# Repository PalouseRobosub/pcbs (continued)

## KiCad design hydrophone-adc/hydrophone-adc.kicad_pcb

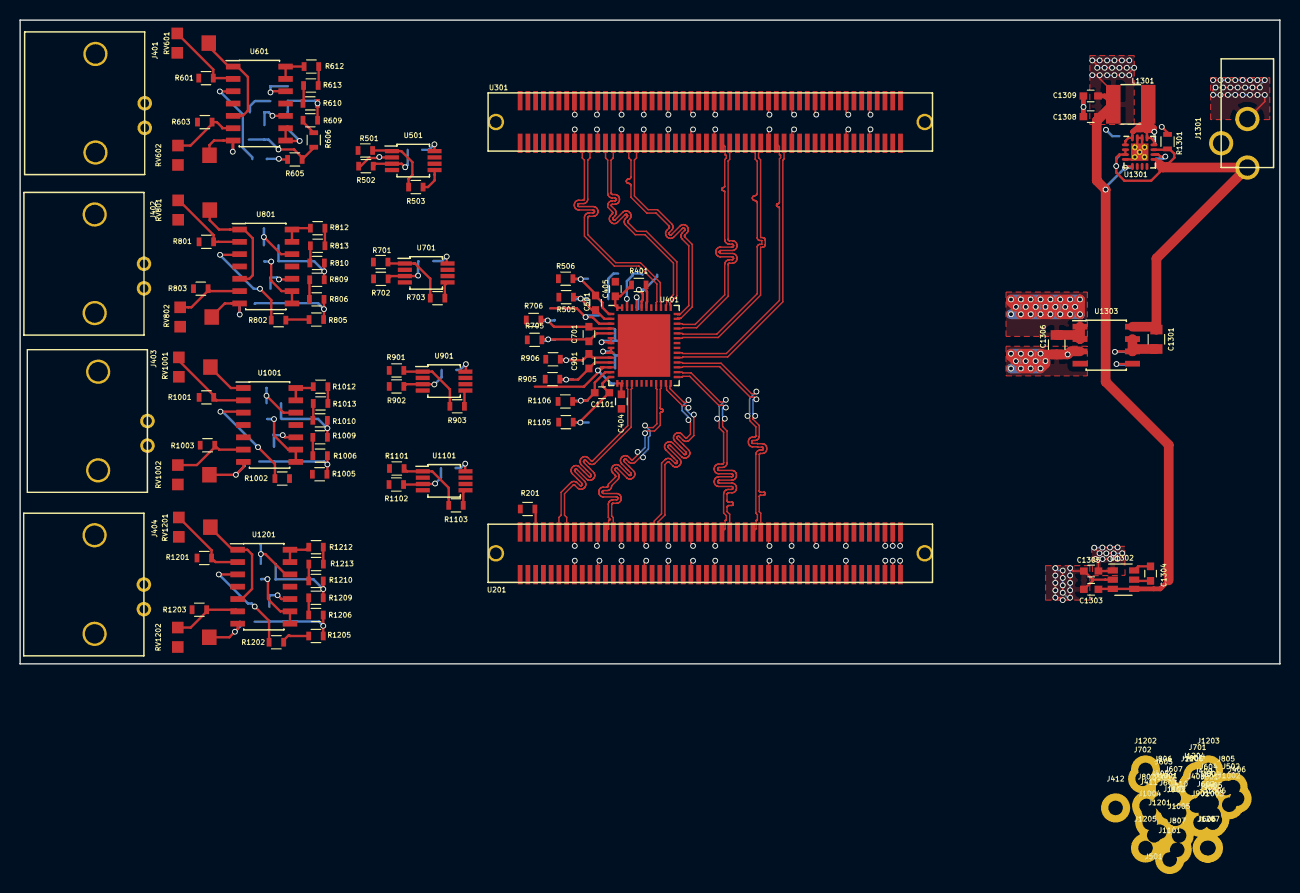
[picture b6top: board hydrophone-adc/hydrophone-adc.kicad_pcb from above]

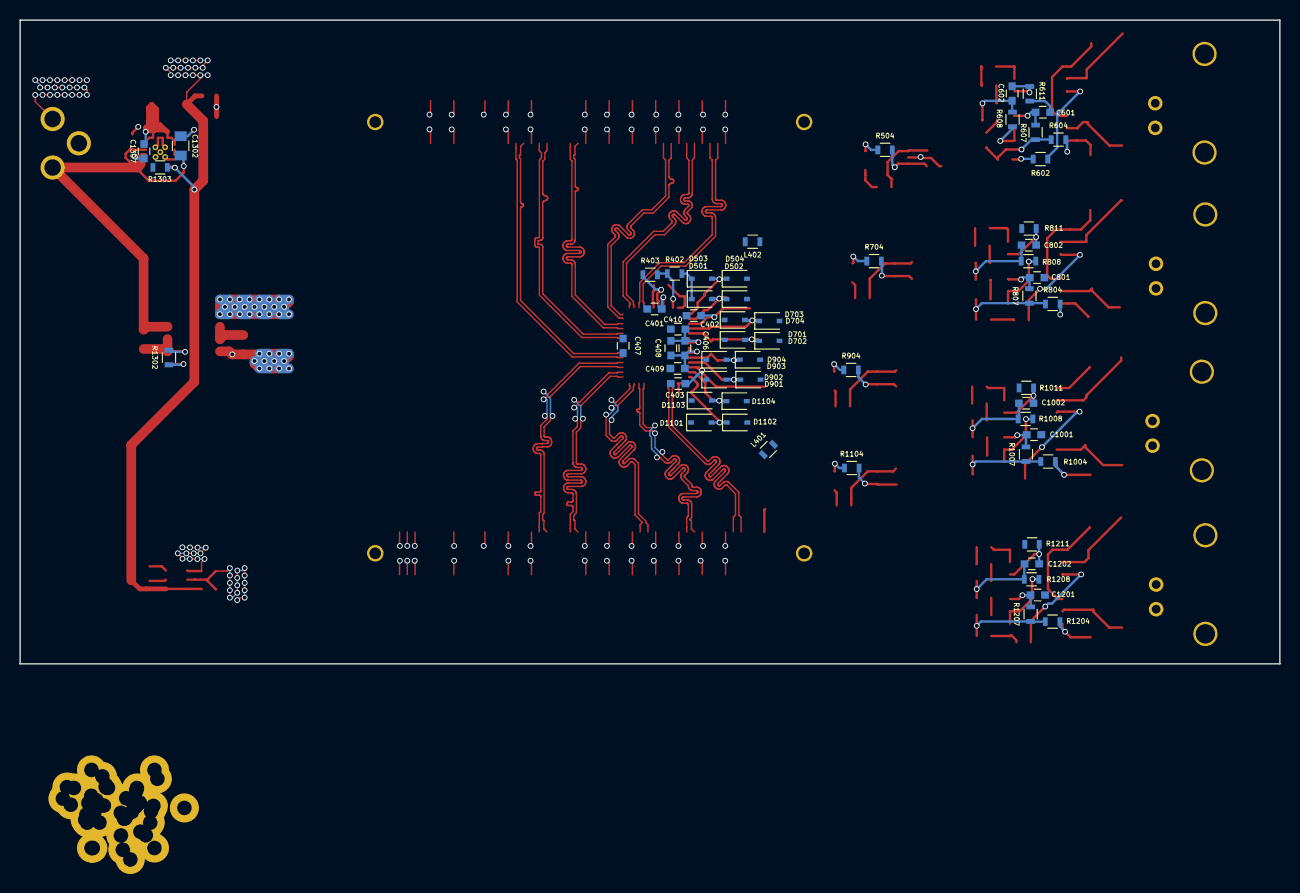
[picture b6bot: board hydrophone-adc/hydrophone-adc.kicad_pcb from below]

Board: 4 copper layers, 129.8 x 66.3 mm, 204 parts (61 on the bottom side), 126 nets.

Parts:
C401, C1304: 1u; C_0603
C402, C403, C404, C405, C406, C407, C409, C410: 100n; C_0603
C408, C1303, C1305: 2.2u; C_0603
C501, C701, C901, C1101: 10n; C_0603
C601, C602, C801, C802, C1001, C1002, C1201, C1202: 1n; C_0603
C1301, C1302, C1306: 10u; C_0805
C1307: 22n; C_0603
C1308, C1309: 22u; C_0603
D501, D502, D503, D504, D701, D702, D703, D704, D901, D902, D903, D904, D1101, D1102, D1103, D1104: D_Schottky; D_SOD-323
J401, J402, J403, J404: CONN_COAXIAL; BNC-Coax-TE
J405, J406, J407, J408, J409, J410, J411, J412, J501, J502, J601, J602, J603, J604, J605, J606, J607, J701, J702, J801, J802, J803, J804, J805, J806, J807, J901, J902, J1001, J1002, J1003, J1004, J1005, J1006, J1007, J1101, J1102, J1201, J1202, J1203, J1204, J1205, J1206, J1207: TEST_1P; Measurement_Point_Round-TH_Big
J1301: BARREL_JACK; BarrelJack-CUI
L401, L402: Ferrite_Bead; R_0603
L1301: 4.7u; Inductor-3.6mm-Pitch-4.0mm-Length-1.5mm-Width
R201, R601, R603, R607, R801, R803, R807, R1001, R1003, R1007, R1201, R1203, R1207, R1301, R1303: 10k; R_0603
R401: 2k; R_0603
R402, R403, R602, R604, R605, R606, R608, R609, R610, R612, R613, R802, R804, R805, R806, R808, R809, R810, R812, R813, R1002, R1004, R1005, R1006, R1008, R1009, R1010, R1012, R1013, R1202, R1204, R1205, R1206, R1208, R1209, R1210, R1212, R1213: 0; R_0603
R501, R502, R503, R504, R701, R702, R703, R704, R901, R902, R903, R904, R1101, R1102, R1103, R1104: 10k .1%; R_0603
R505, R506, R705, R706, R905, R906, R1105, R1106: 100; R_0603
R611, R811, R1011, R1211: 3.16k; R_0603
R1302: 100k; R_0603
RV601, RV602, RV801, RV802, RV1001, RV1002, RV1201, RV1202: POT; TC33X-2
U201: micro-zed-jx1; fci-61083-2x50
U301: micro-zed-jx2; fci-61083-2x50
U401: LTC2171-14; QFN-52-1EP_7x8mm_Pitch0.5mm
U501, U701, U901, U1101: el5170; MSOP-8_3x3mm_Pitch0.65mm
U601, U801, U1001, U1201: LM324; SOIC-14_3.9x8.7mm_Pitch1.27mm
U1301: TS30013; QFN-16-1EP_3x3mm_Pitch0.5mm_ThermalVias
U1302: LM2776; SOT-23-6
U1303: LT1963; SOIC-8_3.9x4.9mm_Pitch1.27mm

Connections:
+1V8: C404.1, C405.1, C407.1, C1306.1, D501.1, D503.1, D701.1, D703.1, D901.1, D903.1, D1101.1, D1103.1, R401.1, R402.2, U201.78, U201.79, U201.80, U301.78, U301.79, U301.80, U401.15, U401.16, U401.34, U401.51, U401.52, U1303.1, U1303.2
+5V: C1303.1, C1308.1, C1309.1, L1301.2, R201.1, R1303.1, U201.57, U201.58, U201.59, U201.60, U301.12, U301.57, U301.58, U301.59, U301.60, U501.6, U601.4, U701.6, U801.4, U901.6, U1001.4, U1101.6, U1201.4, U1301.5, U1302.3, U1302.4
-5V: C1305.1, U501.7, U601.11, U701.7, U801.11, U901.7, U1001.11, U1101.7, U1201.11, U1302.1
/ADC/Diff Conv1/Vin: R501.2, R612.1, R613.1
/ADC/Diff Conv1/Vout+: C501.2, D503.2, D504.1, J406.1, J502.1, R506.2, U401.1
/ADC/Diff Conv1/Vout-: C501.1, D501.2, D502.1, J405.1, J501.1, R505.2, U401.2
/ADC/Diff Conv2/Vin: R701.2, R812.1, R813.1
/ADC/Diff Conv2/Vout+: C701.2, D703.2, D704.1, J408.1, J702.1, R706.2, U401.4
/ADC/Diff Conv2/Vout-: C701.1, D701.2, D702.1, J407.1, J701.1, R705.2, U401.5
/ADC/Diff Conv3/Vin: R901.2, R1012.1, R1013.1
/ADC/Diff Conv3/Vout+: C901.2, D903.2, D904.1, J410.1, J902.1, R906.2, U401.10
/ADC/Diff Conv3/Vout-: C901.1, D901.2, D902.1, J409.1, J901.1, R905.2, U401.11
/ADC/Diff Conv4/Vin: R1101.2, R1212.1, R1213.1
/ADC/Diff Conv4/Vout+: C1101.2, D1103.2, D1104.1, J412.1, J1102.1, R1106.2, U401.13
/ADC/Diff Conv4/Vout-: C1101.1, D1101.2, D1102.1, J411.1, J1101.1, R1105.2, U401.14
/ADC/Filter1/Vin: J401.1, J601.1, R602.1, U601.3
/ADC/Filter2/Vin: J402.1, J801.1, R802.1, U801.3
/ADC/Filter3/Vin: J403.1, J1001.1, R1002.1, U1001.3
/ADC/Filter4/Vin: J404.1, J1201.1, R1202.1, U1201.3
/ADC/MISO: R401.2, U401.46
/ADC/Vcm12: C402.1, U401.3, U501.4, U701.4
/ADC/Vcm34: C403.1, U401.12, U901.4, U1101.4
/Power/Vin: C1301.1, C1302.1, J1301.1, R1301.1, U1301.2, U1301.3, U1301.9, U1301.11, U1303.8
/data_clk+: U301.62, U401.36
/data_clk-: U301.64, U401.35
/fr_clk+: U301.68, U401.32
/fr_clk-: U301.70, U401.31
/out1a+: U301.18, U401.44
/out1a-: U301.20, U401.43
/out1b+: U301.24, U401.42
/out1b-: U301.26, U401.41
/out2a+: U301.30, U401.40
/out2a-: U301.32, U401.39
/out2b+: U301.54, U401.38
/out2b-: U301.56, U401.37
/out3a+: U201.61, U401.30
/out3a-: U201.63, U401.29
/out3b+: U201.53, U401.28
/out3b-: U201.55, U401.27
/out4a+: U201.35, U401.26
/out4a-: U201.37, U401.25
/out4b+: U201.23, U401.24
/out4b-: U201.25, U401.23
/samp_clk+: U201.11, U401.17
/samp_clk-: U201.13, U401.18
/v_good: R1303.2, U301.11, U1301.8
/vccio_en: R1302.1, U301.10, U1303.5
GND: C407.2, C1301.2, C1302.2, C1303.2, C1305.2, C1306.2, C1308.2, C1309.2, J1301.2, L401.1, L402.1, R403.1, R1301.2, R1302.2, U201.15, U201.16, U201.21, U201.22, U201.27, U201.28, U201.33, U201.34, U201.39, U201.40, U201.45, U201.46, U201.51, U201.52, U201.65, U201.66, U201.71, U201.72, U201.77, U201.85, U201.86, U201.95, U201.96, U201.97, U201.98, U201.99, U201.100, U301.15, U301.16, U301.21, U301.22, U301.27, U301.28, U301.33, U301.34, U301.39, U301.40, U301.45, U301.46, U301.51, U301.52, U301.65, U301.66, U301.71, U301.72, U301.77, U301.85, U301.86, U301.91, U301.92, U401.33, U401.47, U1301.4, U1301.14, U1301.15, U1301.17, U1302.2, U1303.3, U1303.6, U1303.7
GNDREF: C401.2, C402.2, C403.2, C404.2, C405.2, C409.1, C410.2, C601.2, C801.2, C1001.2, C1201.2, D502.2, D504.2, D702.2, D704.2, D902.2, D904.2, D1102.2, D1104.2, J401.2, J402.2, J403.2, J404.2, L401.2, L402.2, R502.2, R601.1, R603.1, R611.2, R702.2, R801.1, R803.1, R811.2, R902.2, R1001.1, R1003.1, R1011.2, R1102.2, R1201.1, R1203.1, R1211.2, U401.22, U401.45, U401.49, U401.53, U501.2, U701.2, U901.2, U1101.2
unnamed: C401.1, U401.48
unnamed: C406.1, C408.1, C410.1, U401.6, U401.7
unnamed: C406.2, C408.2, C409.2, U401.8, U401.9
unnamed: C601.1, J604.1, R607.2, U601.10
unnamed: C602.1, J606.1, R611.1, U601.12
unnamed: C602.2, R608.1, R609.1, R610.1
unnamed: C801.1, J804.1, R807.2, U801.10
unnamed: C802.1, J806.1, R811.1, U801.12
unnamed: C802.2, R808.1, R809.1, R810.1
unnamed: C1001.1, J1004.1, R1007.2, U1001.10
unnamed: C1002.1, J1006.1, R1011.1, U1001.12
unnamed: C1002.2, R1008.1, R1009.1, R1010.1
unnamed: C1201.1, J1204.1, R1207.2, U1201.10
unnamed: C1202.1, J1206.1, R1211.1, U1201.12
unnamed: C1202.2, R1208.1, R1209.1, R1210.1
unnamed: C1304.1, U1302.5
unnamed: C1304.2, U1302.6
unnamed: C1307.1, L1301.1, U1301.1, U1301.12, U1301.13, U1301.16
unnamed: C1307.2, U1301.10
unnamed: J602.1, RV601.2, U601.1, U601.5
unnamed: J603.1, R604.2, RV602.2, U601.7
unnamed: J605.1, R608.2, U601.8, U601.9
unnamed: J607.1, R612.2, U601.13, U601.14
unnamed: J802.1, RV801.2, U801.1, U801.5
unnamed: J803.1, R804.2, RV802.2, U801.7
unnamed: J805.1, R808.2, U801.8, U801.9
unnamed: J807.1, R812.2, U801.13, U801.14
unnamed: J1002.1, RV1001.2, U1001.1, U1001.5
unnamed: J1003.1, R1004.2, RV1002.2, U1001.7
unnamed: J1005.1, R1008.2, U1001.8, U1001.9
unnamed: J1007.1, R1012.2, U1001.13, U1001.14
unnamed: J1202.1, RV1201.2, U1201.1, U1201.5
unnamed: J1203.1, R1204.2, RV1202.2, U1201.7
unnamed: J1205.1, R1208.2, U1201.8, U1201.9
unnamed: J1207.1, R1212.2, U1201.13, U1201.14
unnamed: R201.2, U201.5
unnamed: R402.1, R403.2, U401.50
unnamed: R501.1, R503.2, U501.1
unnamed: R502.1, R504.2, U501.3
unnamed: R503.1, R505.1, U501.5
unnamed: R504.1, R506.1, U501.8
unnamed: R601.2, RV601.1, U601.2
unnamed: R602.2, R605.2
unnamed: R603.2, RV602.1, U601.6
unnamed: R604.1, R605.1, R606.1, R607.1
unnamed: R606.2, R609.2
unnamed: R610.2, R613.2
unnamed: R701.1, R703.2, U701.1
unnamed: R702.1, R704.2, U701.3
unnamed: R703.1, R705.1, U701.5
unnamed: R704.1, R706.1, U701.8
unnamed: R801.2, RV801.1, U801.2
unnamed: R802.2, R805.2
unnamed: R803.2, RV802.1, U801.6
unnamed: R804.1, R805.1, R806.1, R807.1
unnamed: R806.2, R809.2
unnamed: R810.2, R813.2
unnamed: R901.1, R903.2, U901.1
unnamed: R902.1, R904.2, U901.3
unnamed: R903.1, R905.1, U901.5
unnamed: R904.1, R906.1, U901.8
unnamed: R1001.2, RV1001.1, U1001.2
unnamed: R1002.2, R1005.2
unnamed: R1003.2, RV1002.1, U1001.6
unnamed: R1004.1, R1005.1, R1006.1, R1007.1
unnamed: R1006.2, R1009.2
unnamed: R1010.2, R1013.2
unnamed: R1101.1, R1103.2, U1101.1
unnamed: R1102.1, R1104.2, U1101.3
unnamed: R1103.1, R1105.1, U1101.5
unnamed: R1104.1, R1106.1, U1101.8
unnamed: R1201.2, RV1201.1, U1201.2
unnamed: R1202.2, R1205.2
unnamed: R1203.2, RV1202.1, U1201.6
unnamed: R1204.1, R1205.1, R1206.1, R1207.1
unnamed: R1206.2, R1209.2
unnamed: R1210.2, R1213.2

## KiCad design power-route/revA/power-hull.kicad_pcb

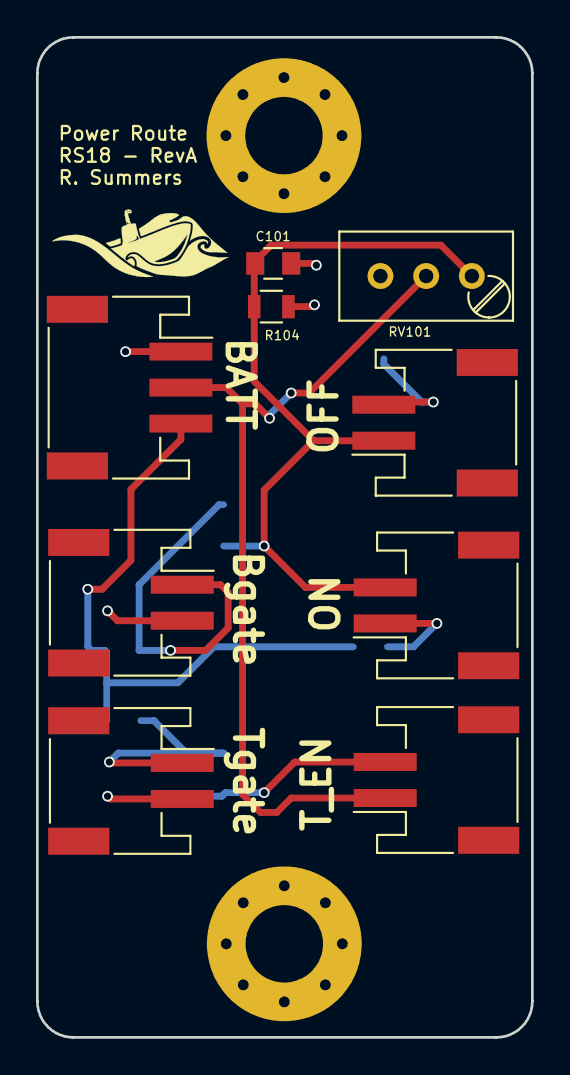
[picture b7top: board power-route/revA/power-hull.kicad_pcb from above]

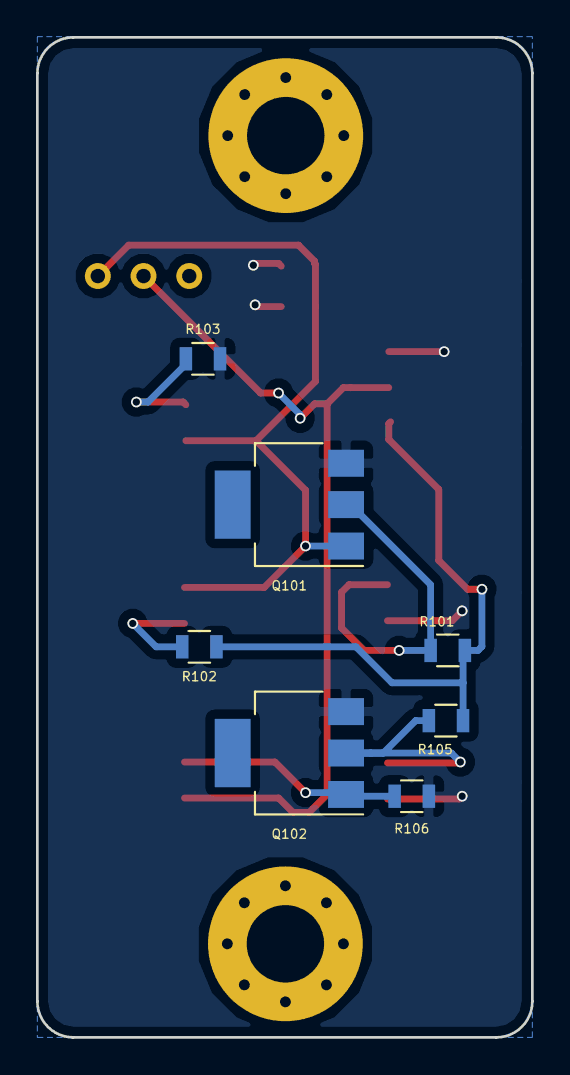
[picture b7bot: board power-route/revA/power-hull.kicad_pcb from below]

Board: 2 copper layers, 27.5 x 55.6 mm, 16 parts (7 on the bottom side), 9 nets.

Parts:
C101: 1u; C_0805
J101: CONN_01X03; JST_PH_S3B-PH-SM4-TB_03x2.00mm_Angled
J102, J103: CONN_01X02; JST_PH_S2B-PH-SM4-TB_02x2.00mm_Angled
Q101, Q102: Q_NMOS_GDS; SOT-223
R101, R104, R105, R106: 10k; R_0805
R102, R103: 1k; R_0805
RV101: POT; Potentiometer_Trimmer_Bourns_3296W
SW101: SW_ON; JST_PH_S2B-PH-SM4-TB_02x2.00mm_Angled
SW102: SW_OFF; JST_PH_S2B-PH-SM4-TB_02x2.00mm_Angled
SW103: SW_TEN; JST_PH_S2B-PH-SM4-TB_02x2.00mm_Angled

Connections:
/Vbattery: J101.3, R101.1, R102.1, R105.1
/Vbulkhead: J101.2, RV101.2, SW103.1
GND: C101.2, J101.1, J102.2, J103.2, Q101.3, Q102.3, R103.2, R104.2, R106.2
unnamed: C101.1, Q101.1, R104.1, RV101.1, SW101.2, SW102.1
unnamed: J102.1, Q101.2, R101.2
unnamed: J103.1, Q102.2, R105.2
unnamed: Q102.1, R106.1, SW103.2
unnamed: R102.2, SW101.1
unnamed: R103.1, SW102.2

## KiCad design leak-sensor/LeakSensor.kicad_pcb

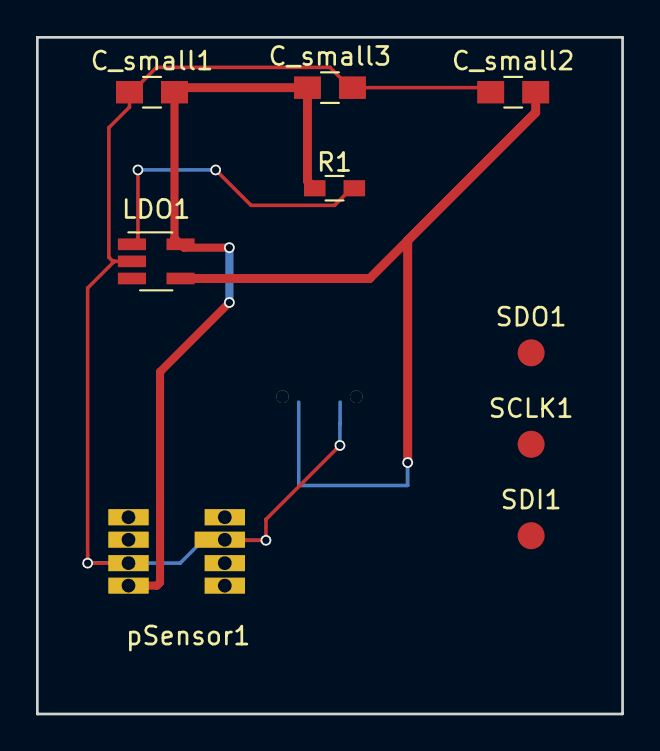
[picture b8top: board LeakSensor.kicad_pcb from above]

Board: 2 copper layers, 32.5 x 37.6 mm, 10 parts (1 on the bottom side), 8 nets.

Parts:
C_small1: 0.1uF; C_0805_HandSoldering
C_small2: 0.47uF; C_0805_HandSoldering
C_small3: 100nF; C_0805_HandSoldering
LDO1: TPS79733QDCKRQ1; SOT-23-5_HandSoldering
P1: Mezzanine-Header; 3mm-10pos-receptacle
R1: 100K; R_0603_HandSoldering
SCLK1: TEST; Measurement_Point_Round-SMD-Pad_Small
SDI1: TEST; Measurement_Point_Round-SMD-Pad_Small
SDO1: TEST; Measurement_Point_Round-SMD-Pad_Small
pSensor1: MS580314BA01-00; MS5803-14BA

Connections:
/CSB: P1.2, pSensor1.3
/GND: C_small1.1, C_small2.1, C_small3.2, LDO1.2, P1.9, pSensor1.2, pSensor1.6
/SCLK: P1.3, SCLK1.1, pSensor1.1
/SDI: P1.7, SDI1.1, pSensor1.7
/SDO: P1.5, SDO1.1, pSensor1.8
/VDD: C_small2.2, LDO1.4, P1.1
/Vreg: C_small1.2, C_small3.1, LDO1.5, R1.1, pSensor1.5
unnamed: LDO1.1, R1.2

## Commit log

2016-10-07 Addition of ATMega128P schematic and I2C Mux library
2016-10-07 Create .gitignore
    Using Github's KiCAD gitignore for now.
2016-10-16 Updated Gitignore to ignore backup files
2016-10-16 Add schematics for thruster signal bus pcb
2016-10-20 Addition of 3,4,6 CUI connectors and Si866x
2016-10-20 Added annular rings to footprint
2016-10-20 Addition of updated CUI5 and Schematic component
2016-10-20 Addition of CUI-5 Footprint
2016-10-21 Initial addition of pneumatics files
    first revision of the pneumatics schematic
2016-10-21 Schematic changes based on the hierarchy
2016-10-21 Connected RST to GPIO
2016-10-21 Initial addition of depth sensor board
2016-10-21 Added robosub library and 5 pin connector
2016-10-21 Updated gitignore to ignore more temporary files
2016-10-21 Changed thruster bus pcb to use 6 pin cui connector and to use 5v and GND
2016-10-21 Added part number to schematic
2016-11-04 Added MOSFET part number
2016-11-04 Added a missing connection
2016-11-04 Changed part number for capacitors
2016-11-04 Added connector part numbers and footprints
2016-11-11 Addition of robosub parts, 3d models, and interface converter board
2016-11-11 Update of Interface Converter to utilize alternate Power LED
2016-11-11 Added AP2112 to library and LEDs to schematic
2016-11-11 Added RJ10 Jack footprint
2016-11-11 Library copy
2016-11-12 Addition of CUI 6 pin 3d model
2016-11-12 Addition of part libraries. Currently updating all components
2016-11-12 Addition of 3D models for all CUI parts
2016-11-12 Schematic finished and Attempted PCB layout
2016-11-12 Update of ATMega schematic to utilize decoupling capacitors and debug LED
2016-11-12 Addition of spacer schematic component
2016-11-12 Made PCB smaller
2016-11-13 Updating a correction to the ATMega schematic
2016-11-13 Addition of Maestro adapter board
2016-11-13 Update of Maestro Adapter post corrections for OSH Park Order
2016-11-13 Updating PCB to utilize 3D models
2016-11-13 Addition of labels for OSH Park printing
2016-11-13 Addition of 3D models to thruster bus
2016-11-13 Correction of CUI-6 to utilize 3D model properly
2016-11-13 Correction of thruster bus to utilize CUI6 3D component
2016-11-13 Addition of LED controller and screw terminal element
2016-11-13 Removing duplicate library entry
2016-11-13 Initial addition of LED controller files
2016-11-13 Addition of LED controller schematic updates
2016-11-13 Additions to LED board
2016-11-13 Update post review of LED controller board
2016-11-13 Addition of completed PCB
2016-11-13 Removed visible reference to footprint
2016-11-14 Added logo to LED Controller
2016-11-16 Cleaned up and organized Maestro Adapter schematic
2016-11-16 Correction to split ATMega1284P schematic to copy in LED controller
2016-11-16 Correcting part number on LEDs
2016-11-16 Correcting rebase error for library footprints
2016-11-16 Cleaning up BNO adapter schematic
2016-11-16 Updating schematic components with proper part numbers
2016-11-16 Modified USB routing and isolated ground from the clock signal
2016-11-16 Huge slew of changes for 3D parts, addition of BNO adapter and digital isolator adapter
2016-11-16 Update to include test points for FTDI signals
2016-11-16 Updating spacers to utilize correct schematic component
2016-11-16 Correcting robosub lib path
2016-11-16 Prettied up schematics for export
2016-11-18 Added updates to interface converter
2016-11-18 Removed merged in duplicate part in robosub lib
2016-11-18 Correction of ATMega1284P schematic to utilize proper oscilator symbol
2016-11-18 Addition of 3d importing script
2016-11-18 Rearranged PCB, removed LEDs from depth sensor schematic
2016-11-19 Routing completed
2016-11-19 Changed to just GND fill
2016-11-20 Redid some connections
2016-11-23 Routing completed(if nothing is seen as incorrect)
2016-12-02 Removed extra mounting holes, added logo, moved header pins
2016-12-04 Correction to bom generator for quantity definitions
2016-12-04 Addition of optional prefix
2016-12-04 Addition of BOM generation script
2016-12-05 Update of foot prints library to include 3MM mezzanine connector
2016-12-05 Updating footprints to show outlines
2016-12-05 Addition of Digital Isolator Rev B
2016-12-05 changed part number for mezzanine connector
2016-12-05 Added footprint of mezzanine header/fixed routing
2016-12-15 changed connectors/fixed labels/fixed vias/extra room for header
2016-12-15 Added test points
2016-12-23 added part number/changed footprint for connectors, moved clk
2016-12-27 Added in pulldown resistor to MUX reset
2016-12-27 Added robosub logo
2016-12-27 Addition of rev B for the interface converter
2016-12-27 Correction to interface board schematic
2017-01-23 Updated BOM generator script to properly use prefixes
2017-01-27 Addition of power case files
2017-01-27 Addition of silkscreen and 2xN pin header
2017-01-27 addition of pin labels to power case
2017-01-27 addition of pin labels to bulkhead board
2017-01-27 changed pin labels and position
2017-01-27 Reloaded netlist
2017-01-28 more finalization
2017-02-05 Addition of Rev2 for depth sensor
2017-02-10 Correction of BNO to new mezzanine
2017-02-10 Added in new revision folder
2017-02-10 Added lipo-charger project
2017-02-16 Create leak-sensor
2017-02-17 added leak sensor files to pcbs folder
2017-02-18 added lipo-charger
2017-02-18 added lipo libraries
2017-02-18 more changes almost done
2017-02-25 Addition of revC interface converter
2017-02-25 Addition of revC of interface converter with ME spec
2017-02-25 Addition of RevC digital isolator per ME spec
2017-02-25 Addition of BNO adapter as per ME spec
2017-02-25 Need to figure out mosfets
2017-02-25 Chose mosfets for balancer
2017-02-25 Addition of depth sensor and led controller per ME spec
2017-02-27 Addition of revised LED controller
2017-02-27 Update of ATMega schematic
2017-02-28 Cleaning up git repo and adding 3d model files
2017-02-28 Resetting rev a of maestro adapter
2017-02-28 Addition of updated maestro adapter
2017-02-28 Addition of VRML flattener
2017-03-02 Addition of VRML v2 model files and finished BNO adapter
2017-03-03 Addition of 3mm support
2017-03-04 initinal eddition of pressure tester
2017-03-05 second eddition of presure tester
2017-03-05 remove files
2017-03-05 interface-converter-plugin added
2017-03-09 Addition of completed pneumatics controller
2017-03-09 Corrected ATMega schematic
2017-03-09 Modified silkscreen on pneumatics
2017-03-09 converted edge-cut mounting holes to KiCAD components
2017-03-09 First eddition of interface converter adapter
2017-03-09 Added labels and moved border slightly
2017-03-10 Changed gpio pins to adc on uC
2017-03-10 Corrected name on interface converter adapter
2017-03-18 Updated and modularized reed-switch layout
2017-03-18 Corrected a number of footprint components
2017-03-23 Implemented main circuit for bq24753a
2017-03-27 Completed connections between bq76920, bq24753a, and uC
2017-03-27 Forgot to save file
2017-04-01 Leak Sensor WIP
2017-05-10 Added footprint for CUI PDM2
2017-09-05 Addition of Carter Moore's power box PCB
2017-11-14 Added changes from pneumatics project and leakSensor schematic
2017-11-14 Changed wiring related to LED's
2017-11-14 The power system schematic in its infancy
2017-12-23 Added in power routing board for driving POWERFET gates
2017-12-24 Corrected potentionmeter part number
2017-12-27 Corrected power source on keep-alive for VBulkhead and set clearance to zero
2017-12-27 Added in RS18 demarcation
2017-12-27 Added in mounting holes and rounded corners
2017-12-31 Moved power-hull to power-route and added revA order
2017-12-31 Added in higher stacking and moved BNCs forward
2017-12-31 Added in final RevB design
2017-12-31 DRC is now passing and preliminary layout is complete.
2017-12-31 Addition of completed input buffer and filtering as well as differential conversion
2017-12-31 Added in the 3d model for the higher stacking connectors
2017-12-31 Finished differential routing and plane layout
2017-12-31 Moved hydrophone ADC revs into folders
2017-12-31 Addition of partially routed board
2017-12-31 Adding stuff i guess?
2017-12-31 Added LEDs to board and schematic
2017-12-31 Updated hydrophone board post review
2017-12-31 reverted revA back to originals
2017-12-31 Added Robosub logo to hydrophone board
2017-12-31 Added 3D model for 6-UFDFN
2017-12-31 Added changelist to ADC board
2017-12-31 Cleaned up schematics
2017-12-31 Moved a few silkscreens
2017-12-31 Addition of finished ADC schematics and beginning of header connections
2017-12-31 Added Rev 2
2017-12-31 Addition of MicroZed carrier start and initial components
2017-12-31 Removed relayControl PCB
2017-12-31 Removed power_case PCB
2018-01-27 Updated BOM generator for simplicity
2018-02-03 Added changes made by KiCad.
2018-02-07 Added changes made by KiCad. And a change made in the BOM.
2018-02-07 Added in RevB of power route
2018-02-17 Fixed labels and visualization of RevC
2018-02-17 Added mounting holes
2018-02-17 Corrected kicad 3d parts visualization and updated dual potentiometer chip to utilize 2.5V range device
2018-02-17 Added final revC revision
2018-02-17 Added in RevC schematic changes for HydroZynq
2018-04-18 Fixed some visual things on the schematic. Nothing changed in the PCB.
2018-04-20 Added new connector types to the signal outputs. Need to make a different footprint, see datasheet.
2018-05-10 Rerouted the PCB for the smaller pitch connector. The DRC rules checked out.
2018-05-10 Generated Gerbers to check final layout. Added name to PCB.
2018-06-06 Added some switches corrected/saved by KiCad.
2018-06-11 Started making high level blocks for the items in the overall system and created a library for them local to the project.
2018-06-12 Got most of the system-schematic started. And added more to the system-blocks.
2018-06-13 Added more of the power system to the schematic. Saved some components on the power-route schematic.
2018-06-19 Almost done with the schematic. Need to add thruster power connection.
2018-09-06 Added the files I've made for the demo sumo robot control.
2018-09-26 Added the last two changes made to the project.
